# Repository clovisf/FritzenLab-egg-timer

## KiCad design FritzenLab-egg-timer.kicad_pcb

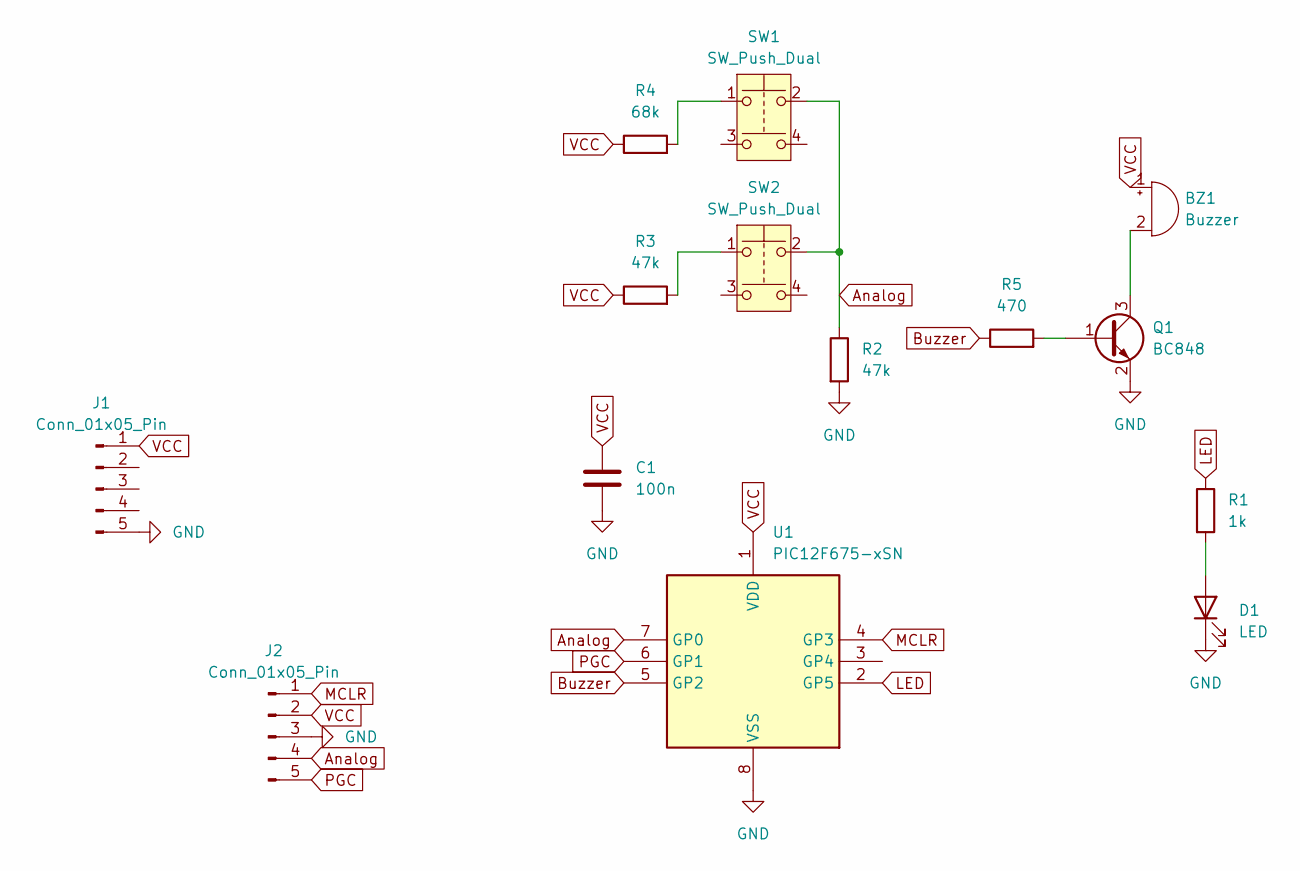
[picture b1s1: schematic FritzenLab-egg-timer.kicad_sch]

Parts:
BZ1: Buzzer; Buzzer_12x9.5RM7.6
C1: 100n; C_0805_2012Metric
D1: LED; LED_D5.0mm
J1, J2: Conn_01x05_Pin; PinHeader_1x05_P2.54mm_Vertical
Q1: BC848; SOT-23
R1: 1k; R_0805_2012Metric
R2, R3: 47k; R_0805_2012Metric
R4: 68k; R_0805_2012Metric
R5: 470; R_0805_2012Metric
SW1, SW2: SW_Push_Dual; SW_SPST_PTS810
U1: PIC12F675-xSN; SOIC-8_3.9x4.9mm_P1.27mm

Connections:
Analog: J2.4, R2.1, SW1.2, SW2.2, U1.7 (GP0)
Buzzer: R5.1, U1.5 (GP2)
GND: C1.2, D1.1 (K), J1.5, J2.3, Q1.2 (E), R2.2, U1.8 (VSS)
LED: R1.1, U1.2 (GP5)
MCLR: J2.1, U1.4 (GP3)
unnamed: BZ1.2 (-), Q1.3 (C)
unnamed: D1.2 (A), R1.2
unnamed: Q1.1 (B), R5.2
unnamed: R3.2, SW2.1
unnamed: R4.2, SW1.1
PGC: J2.5, U1.6 (GP1)
VCC: BZ1.1 (+), C1.1, J1.1, J2.2, R3.1, R4.1, U1.1 (VDD)

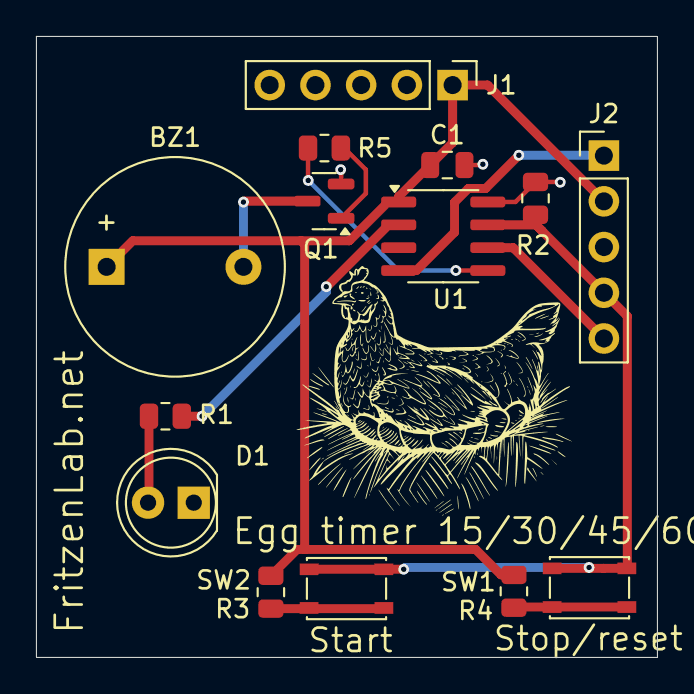
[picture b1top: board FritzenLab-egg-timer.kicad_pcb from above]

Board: 2 copper layers, 34.5 x 34.5 mm, 14 parts (0 on the bottom side), 12 nets.

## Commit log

2024-10-15 backups
2024-10-16 created PCB but not finished
2024-10-16 almost finished PCB layout
2024-10-18 Gerber generated
2025-01-19 edited code
2025-07-11 minimally working code
2025-07-12 final code version (01)
2025-07-13 implemented watchdog
    Implemented watchdog for resetting while counting time
2025-08-09 implemented reset (stop)
    implemented reset (stop button)
2025-08-09 stable and finished version
    Everything proposed is implemented, stable and finished version.
2025-08-09 added while(1) in final buzzer
    Added while(1) to activate watchdog after final buzzer sounds.
2026-05-03 fixed timing and counting bugs
    fixed timing and counting bugs, Claude.ai and ChatGPT helped me on that
